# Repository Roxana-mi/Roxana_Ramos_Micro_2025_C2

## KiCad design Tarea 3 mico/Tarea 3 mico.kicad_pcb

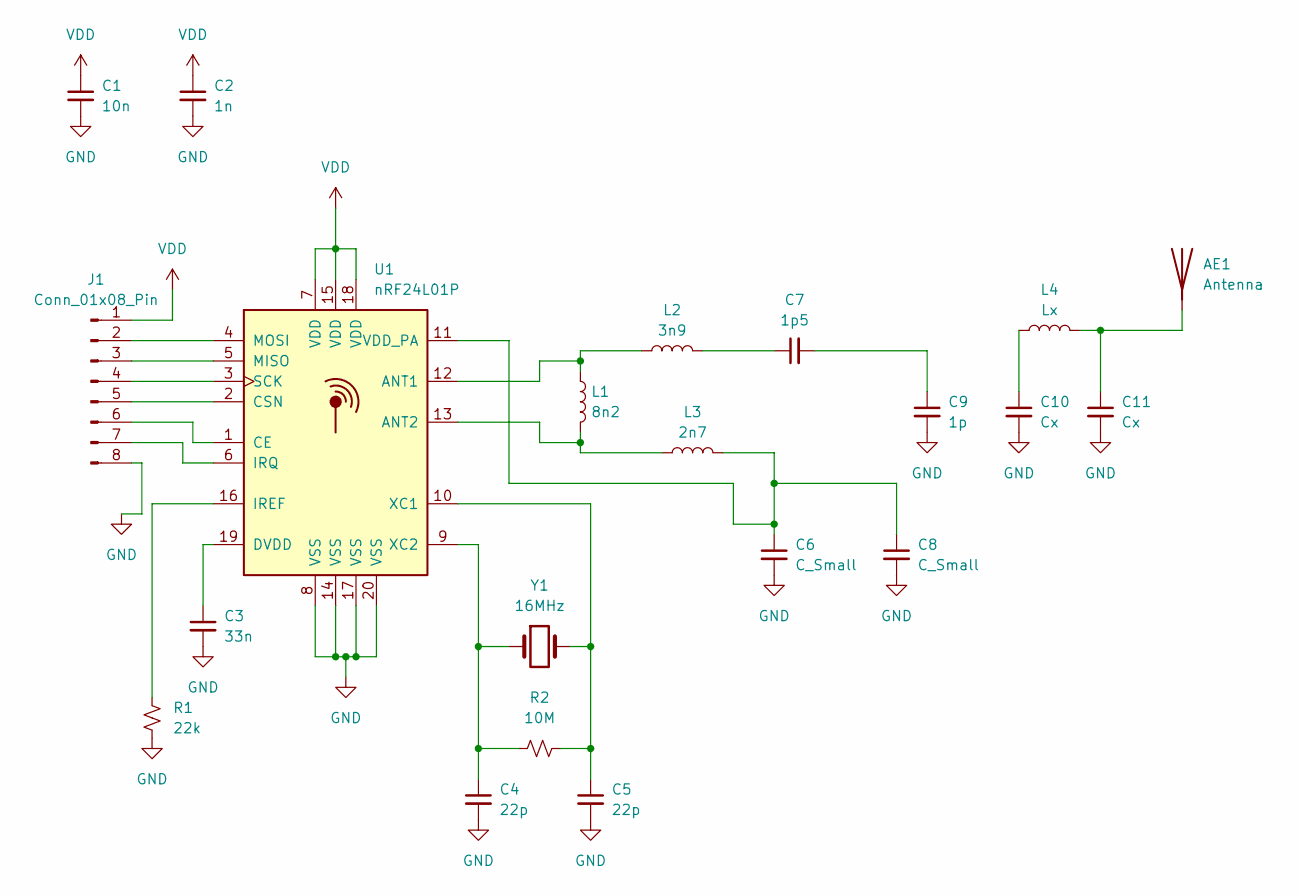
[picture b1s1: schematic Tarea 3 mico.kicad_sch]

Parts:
AE1: Antenna
C1: 10n; C_0402_1005Metric
C2: 1n; C_0402_1005Metric
C3: 33n; C_0402_1005Metric
C4, C5: 22p; C_0402_1005Metric
C6, C8: C_Small; C_0402_1005Metric
C7: 1p5; C_0402_1005Metric
C9: 1p; C_0402_1005Metric
C10, C11: Cx; C_0402_1005Metric
J1: Conn_01x08_Pin; Hirose_DF13-08P-1.25DSA_1x08_P1.25mm_Vertical
L1: 8n2; L_0402_1005Metric
L2: 3n9; L_0402_1005Metric
L3: 2n7; L_0402_1005Metric
L4: Lx; L_0402_1005Metric
R1: 22k; R_0402_1005Metric
R2: 10M; R_0402_1005Metric
U1: nRF24L01P; QFN-20-1EP_4x4mm_P0.5mm_EP2.5x2.5mm
Y1: 16MHz; Crystal_SMD_3215-2Pin_3.2x1.5mm

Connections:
GND: C1.2, C2.2, C3.2, C4.2, C5.2, C6.2, C8.2, C9.2, C10.2, C11.2, J1.8, R1.2, U1.8 (VSS), U1.14 (VSS), U1.17 (VSS), U1.20 (VSS)
unnamed: AE1.1, C11.1, L4.2
unnamed: C7.1, L2.2
unnamed: C7.2, C9.1
unnamed: C10.1, L4.1
unnamed: J1.2, U1.4 (MOSI)
unnamed: J1.3, U1.5 (MISO)
unnamed: J1.4, U1.3 (SCK)
unnamed: J1.5, U1.2 (CSN)
unnamed: J1.6, U1.1 (CE)
unnamed: J1.7, U1.6 (IRQ)
unnamed: L1.1, L2.1, U1.12 (ANT1)
unnamed: L1.2, L3.1, U1.13 (ANT2)
unnamed: C3.1, U1.19 (DVDD)
unnamed: R1.1, U1.16 (IREF)
unnamed: C6.1, C8.1, L3.2, U1.11 (VDD_PA)
unnamed: C5.1, R2.2, U1.10 (XC1), Y1.2
unnamed: C4.1, R2.1, U1.9 (XC2), Y1.1
VDD: C1.1, C2.1, J1.1, U1.7 (VDD), U1.15 (VDD), U1.18 (VDD)

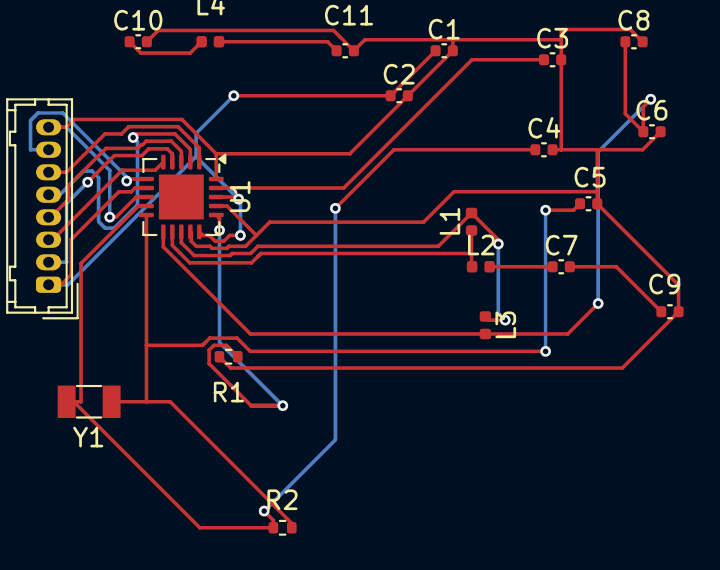
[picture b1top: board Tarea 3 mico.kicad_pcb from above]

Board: 2 copper layers, 20 parts (0 on the bottom side), 19 nets.

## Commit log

2025-06-13 Tarea 2
2025-08-22 Create Tarea 4
2025-08-22 Update Tarea 4
2025-08-23 Tarea6
2025-08-24 Create Tarea 5
2025-08-24 Create ejercisio 1 del video
2025-08-24 Create Ejercisiop 2 del video
2025-08-24 Create Ejercio 3 del video
2025-08-24 Create Ejercisio 4 del video
2025-08-24 Create Ejercisio 5 del video
2025-08-24 Rename Ejercio 3 del video to Ejercicio 3 del video
2025-08-24 Create Ejercicio 6 del video
